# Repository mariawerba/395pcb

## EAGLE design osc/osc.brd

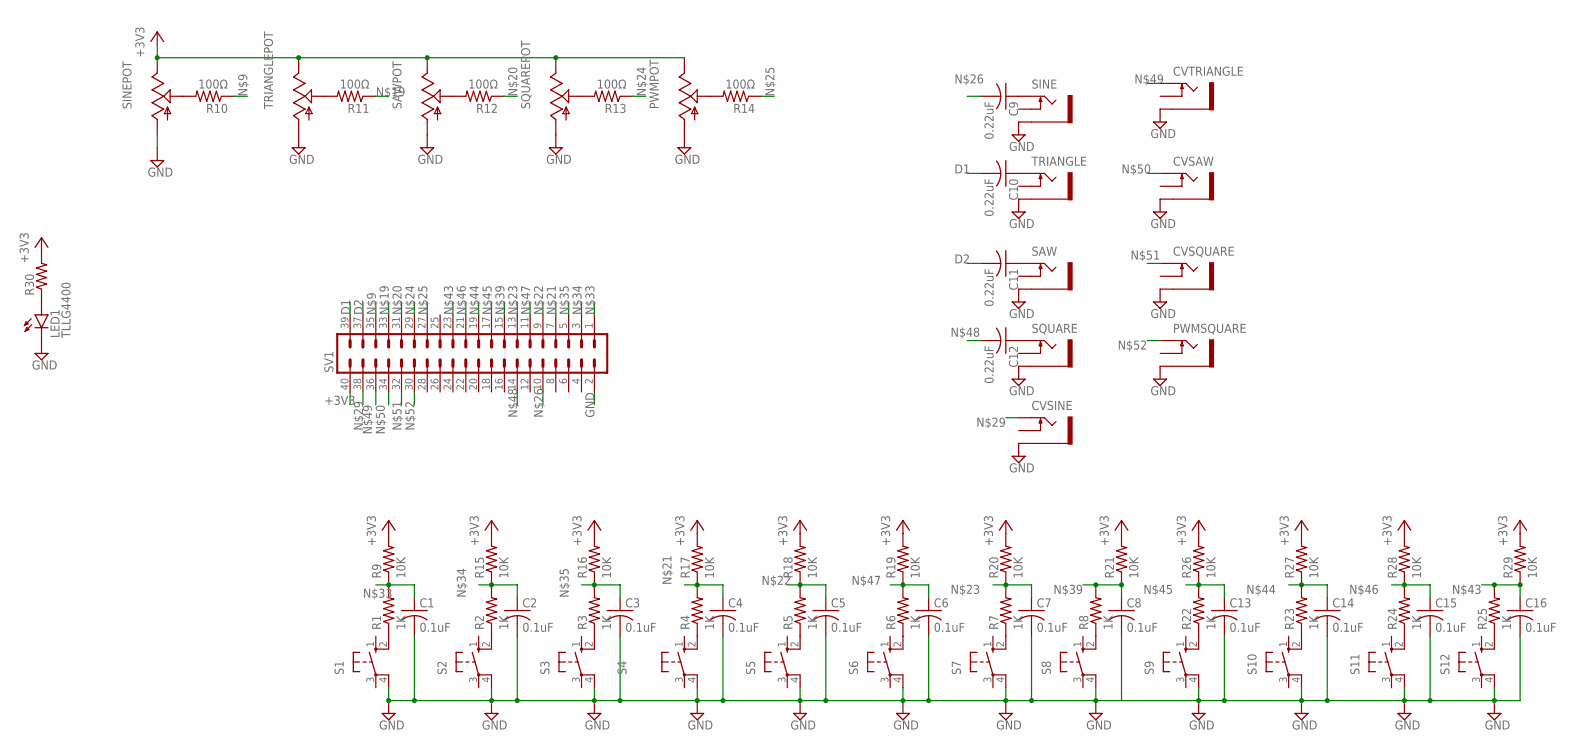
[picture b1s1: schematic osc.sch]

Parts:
C1, C2, C3, C4, C5, C6, C7, C8, C13, C14, C15, C16: 0.1uF; C025-024X044
C9, C10, C11, C12: 0.22uF; C025-024X044
CVSAW: THONKICONNNEW; WQP-PJ301M-12_JACK
CVSINE: THONKICONNNEW; WQP-PJ301M-12_JACK
CVSQUARE: THONKICONNNEW; WQP-PJ301M-12_JACK
CVTRIANGLE: THONKICONNNEW; WQP-PJ301M-12_JACK
LED1: TLLG4400; LED3MM
PWMPOT: 9MM_SNAP-IN_POT_; 9MM_SNAP-IN_POT
PWMSQUARE: THONKICONNNEW; WQP-PJ301M-12_JACK
R1, R2, R3, R4, R5, R6, R7, R8, R22, R23, R24, R25: 1K; 0207/10
R9, R15, R16, R17, R18, R19, R20, R21, R26, R27, R28, R29: 10K; 0207/10
R10, R11, R12, R13, R14: 100Ω; 0207/10
R30: R-US_0207/10; 0207/10
S1, S2, S3, S4, S5, S6, S7, S8, S9, S10, S11, S12: 10-XX; B3F-10XX
SAW: THONKICONNNEW; WQP-PJ301M-12_JACK
SAWPOT: 9MM_SNAP-IN_POT_; 9MM_SNAP-IN_POT
SINE: THONKICONNNEW; WQP-PJ301M-12_JACK
SINEPOT: 9MM_SNAP-IN_POT_; 9MM_SNAP-IN_POT
SQUARE: THONKICONNNEW; WQP-PJ301M-12_JACK
SQUAREPOT: 9MM_SNAP-IN_POT_; 9MM_SNAP-IN_POT
SV1: MA20-2
TRIANGLE: THONKICONNNEW; WQP-PJ301M-12_JACK
TRIANGLEPOT: 9MM_SNAP-IN_POT_; 9MM_SNAP-IN_POT

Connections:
+3V3: PWMPOT.3 (E), R9.2, R15.2, R16.2, R17.2, R18.2, R19.2, R20.2, R21.2, R26.2, R27.2, R28.2, R29.2, R30.2, SAWPOT.3 (E), SINEPOT.3 (E), SQUAREPOT.3 (E), SV1.40, TRIANGLEPOT.3 (E)
D1: C10.2, SV1.39
D2: C11.2, SV1.37
GND: C1.2, C2.2, C3.2, C4.2, C5.2, C6.2, C7.2, C8.2, C13.2, C14.2, C15.2, C16.2, CVSAW.P$3_SLEEVE (SLEEVE), CVSINE.P$3_SLEEVE (SLEEVE), CVSQUARE.P$3_SLEEVE (SLEEVE), CVTRIANGLE.P$3_SLEEVE (SLEEVE), LED1.K (C), PWMPOT.1 (A), PWMSQUARE.P$3_SLEEVE (SLEEVE), S1.4 (P1), S2.4 (P1), S3.4 (P1), S4.4 (P1), S5.4 (P1), S6.4 (P1), S7.4 (P1), S8.4 (P1), S9.4 (P1), S10.4 (P1), S11.4 (P1), S12.4 (P1), SAW.P$3_SLEEVE (SLEEVE), SAWPOT.1 (A), SINE.P$3_SLEEVE (SLEEVE), SINEPOT.1 (A), SQUARE.P$3_SLEEVE (SLEEVE), SQUAREPOT.1 (A), SV1.2, TRIANGLE.P$3_SLEEVE (SLEEVE), TRIANGLEPOT.1 (A)
unnamed: R1.1, S1.2 (S1)
unnamed: R2.1, S2.2 (S1)
unnamed: R3.1, S3.2 (S1)
unnamed: R4.1, S4.2 (S1)
unnamed: R6.1, S6.2 (S1)
unnamed: R7.1, S7.2 (S1)
unnamed: R8.1, S8.2 (S1)
unnamed: R5.1, S5.2 (S1)
unnamed: R10.1, SV1.35
unnamed: C9.1, SINE.P$1_TIP (TIP)
unnamed: C10.1, TRIANGLE.P$1_TIP (TIP)
unnamed: C11.1, SAW.P$1_TIP (TIP)
unnamed: C12.1, SQUARE.P$1_TIP (TIP)
unnamed: R10.2, SINEPOT.2 (S)
unnamed: R11.2, TRIANGLEPOT.2 (S)
unnamed: R12.2, SAWPOT.2 (S)
unnamed: R13.2, SQUAREPOT.2 (S)
unnamed: PWMPOT.2 (S), R14.2
unnamed: R11.1, SV1.33
unnamed: R12.1, SV1.31
unnamed: C4.1, R4.2, R17.1, SV1.7
unnamed: C5.1, R5.2, R18.1, SV1.9
unnamed: C7.1, R7.2, R20.1, SV1.13
unnamed: R13.1, SV1.29
unnamed: R14.1, SV1.27
unnamed: C9.2, SV1.10
unnamed: LED1.A, R30.1
unnamed: CVSINE.P$1_TIP (TIP), SV1.38
unnamed: C1.1, R1.2, R9.1, SV1.1
unnamed: C2.1, R2.2, R15.1, SV1.3
unnamed: C3.1, R3.2, R16.1, SV1.5
unnamed: R23.1, S10.2 (S1)
unnamed: C8.1, R8.2, R21.1, SV1.15
unnamed: R24.1, S11.2 (S1)
unnamed: R25.1, S12.2 (S1)
unnamed: R22.1, S9.2 (S1)
unnamed: C16.1, R25.2, R29.1, SV1.23
unnamed: C14.1, R23.2, R27.1, SV1.19
unnamed: C13.1, R22.2, R26.1, SV1.17
unnamed: C15.1, R24.2, R28.1, SV1.21
unnamed: C6.1, R6.2, R19.1, SV1.11
unnamed: C12.2, SV1.14
unnamed: CVTRIANGLE.P$1_TIP (TIP), SV1.36
unnamed: CVSAW.P$1_TIP (TIP), SV1.34
unnamed: CVSQUARE.P$1_TIP (TIP), SV1.32
unnamed: PWMSQUARE.P$1_TIP (TIP), SV1.30

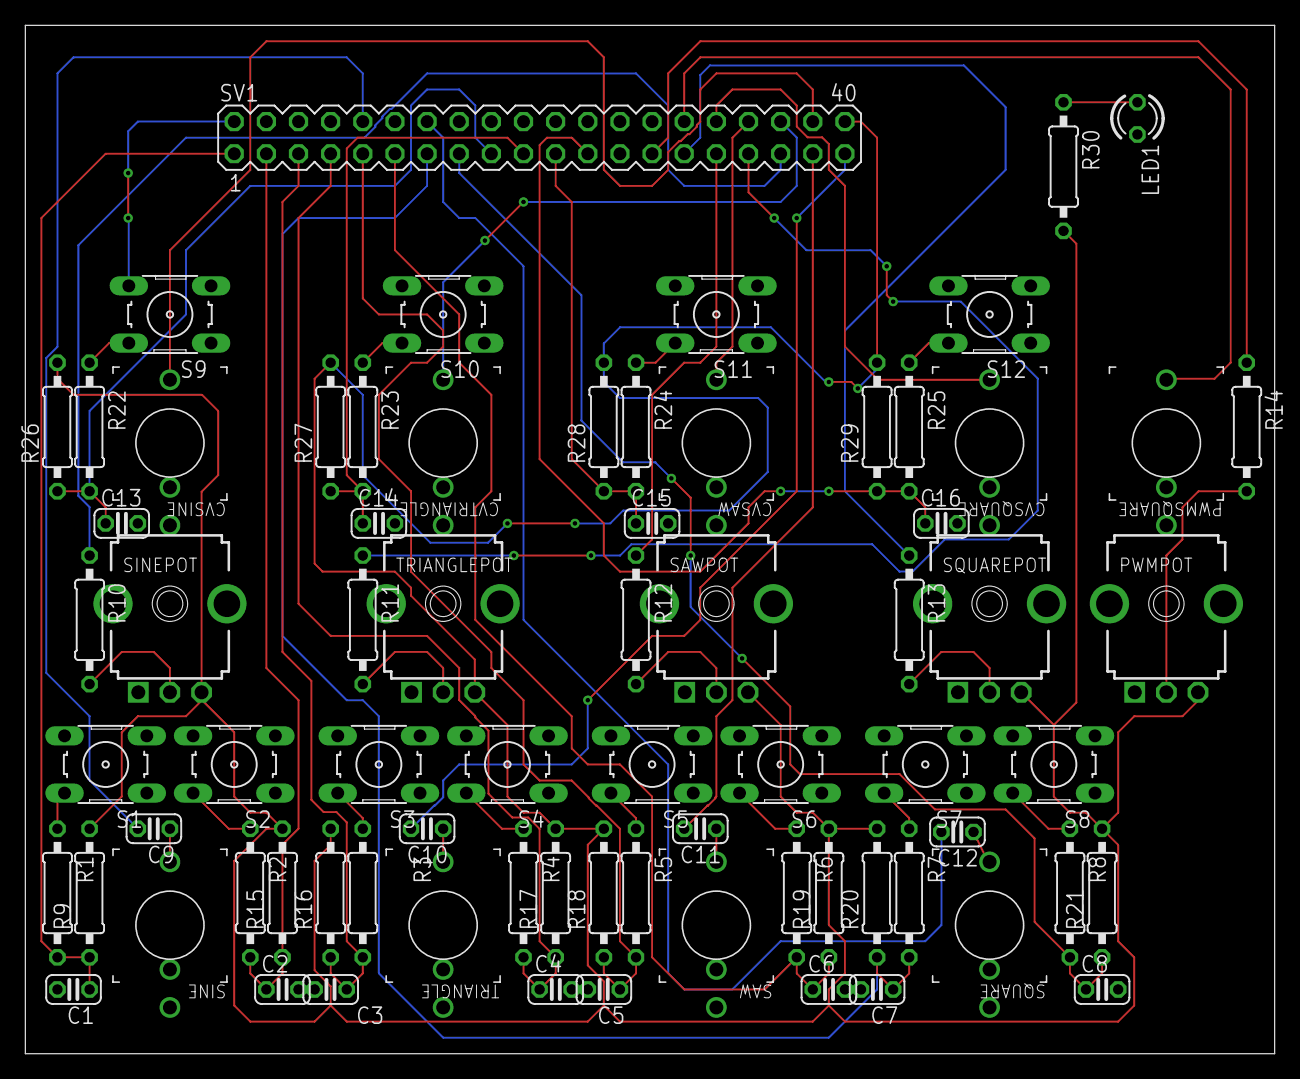
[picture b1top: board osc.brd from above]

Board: 2 copper layers, 98.7 x 81.3 mm, 74 parts (0 on the bottom side), 50 nets.

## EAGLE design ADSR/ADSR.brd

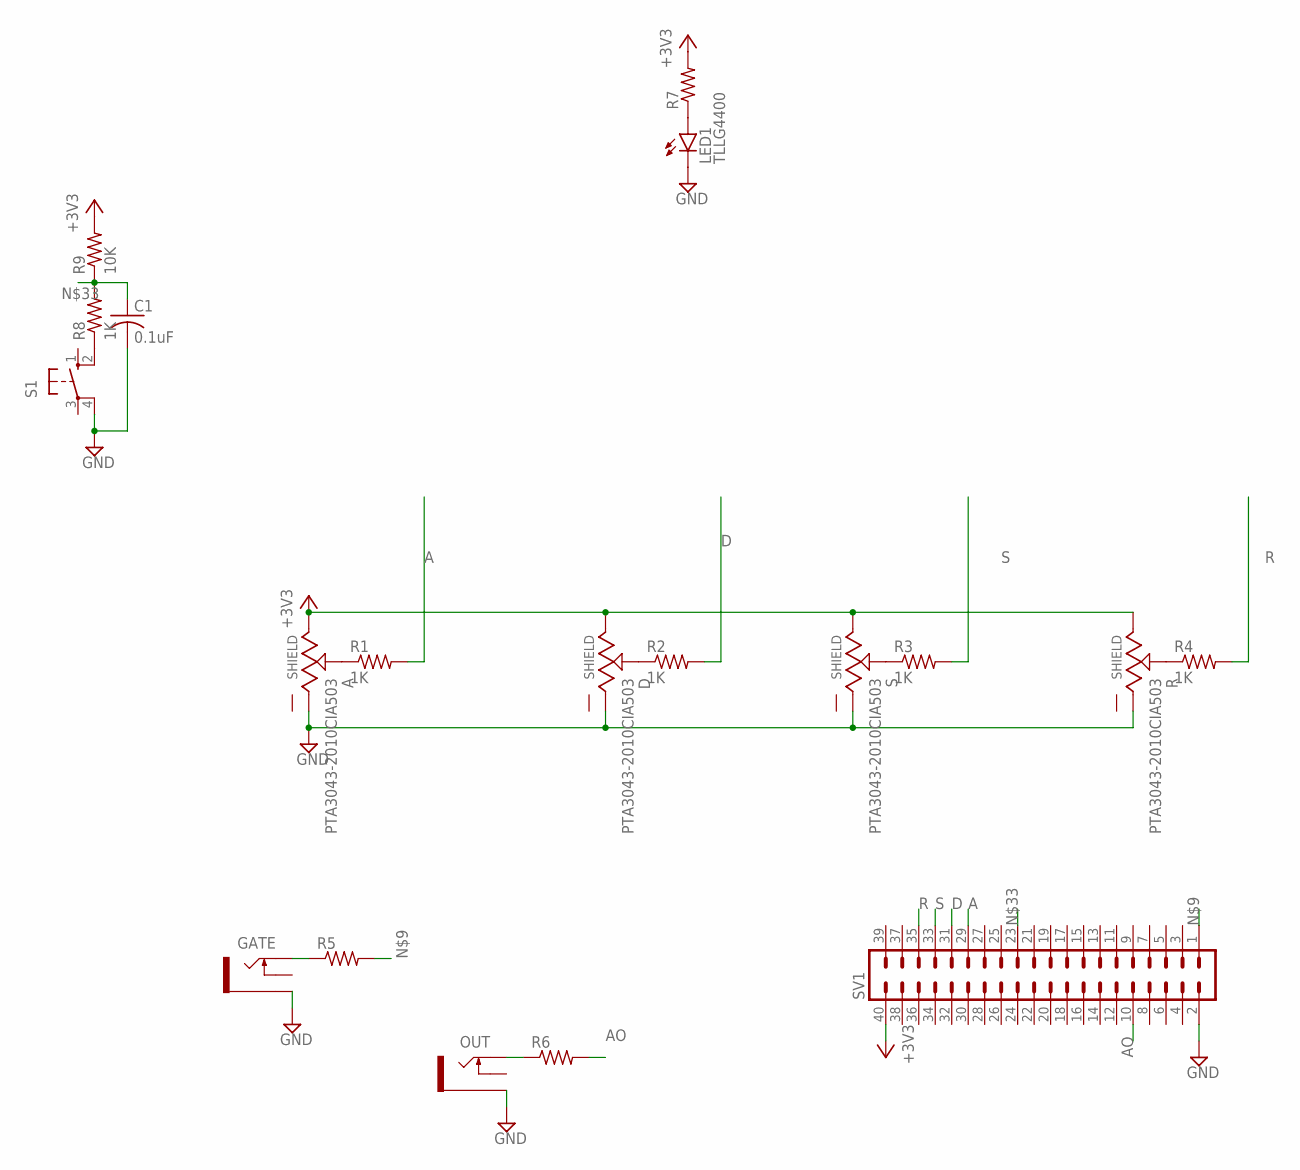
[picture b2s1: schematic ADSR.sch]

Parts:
A: PTA3043-2010CIA503; TRIM_PTA3043-2010CIA503
C1: 0.1uF; C025-024X044
D: PTA3043-2010CIA503; TRIM_PTA3043-2010CIA503
GATE: THONKICONNNEW; WQP-PJ301M-12_JACK
LED1: TLLG4400; LED3MM
OUT: THONKICONNNEW; WQP-PJ301M-12_JACK
R: PTA3043-2010CIA503; TRIM_PTA3043-2010CIA503
R1, R2, R3, R4, R8: 1K; 0207/10
R5, R6, R7: R-US_0207/10; 0207/10
R9: 10K; 0207/10
S: PTA3043-2010CIA503; TRIM_PTA3043-2010CIA503
S1: 10-XX; B3F-10XX
SV1: MA20-2

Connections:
+3V3: A.1, D.1, R.1, R7.2, R9.2, S.1, SV1.40
A: R1.2, SV1.29
AO: R6.2, SV1.10
D: R2.2, SV1.31
GND: A.3, C1.2, D.3, GATE.P$3_SLEEVE (SLEEVE), LED1.K (C), OUT.P$3_SLEEVE (SLEEVE), R.3, S.3, S1.4 (P1), SV1.2
unnamed: A.2, R1.1
unnamed: D.2, R2.1
unnamed: R3.1, S.2
unnamed: R.2, R4.1
unnamed: OUT.P$1_TIP (TIP), R6.1
unnamed: LED1.A, R7.1
unnamed: R8.1, S1.2 (S1)
unnamed: R5.2, SV1.1
unnamed: GATE.P$1_TIP (TIP), R5.1
unnamed: C1.1, R8.2, R9.1, SV1.23
R: R4.2, SV1.35
S: R3.2, SV1.33

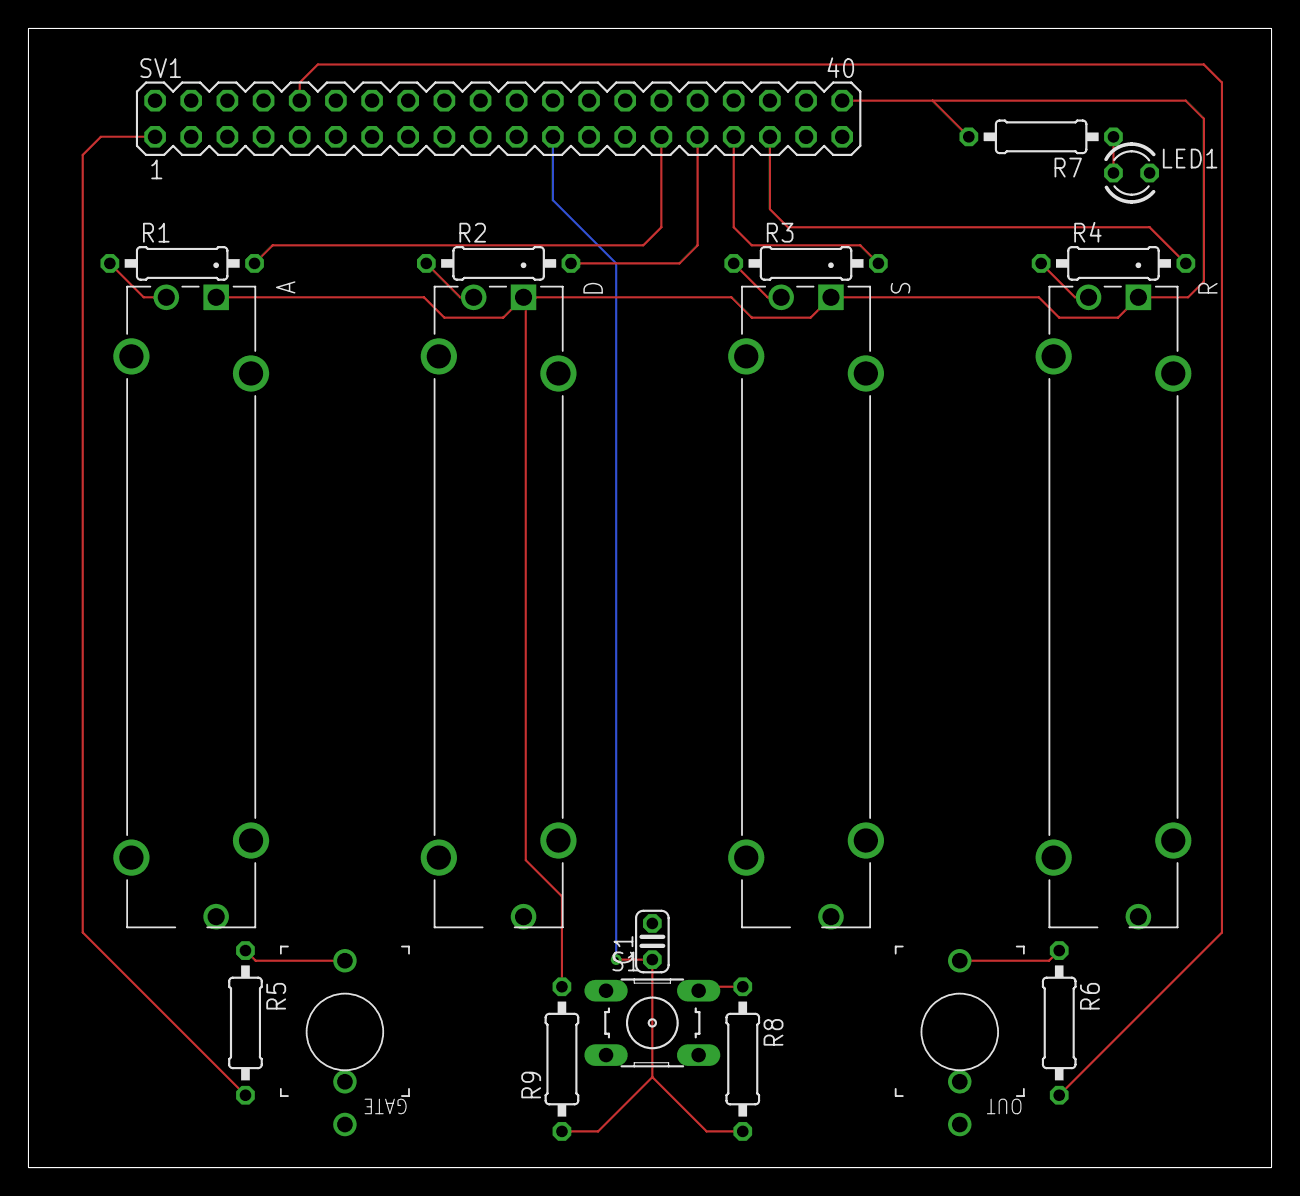
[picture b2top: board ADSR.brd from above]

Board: 2 copper layers, 87.3 x 80.0 mm, 19 parts (0 on the bottom side), 17 nets.

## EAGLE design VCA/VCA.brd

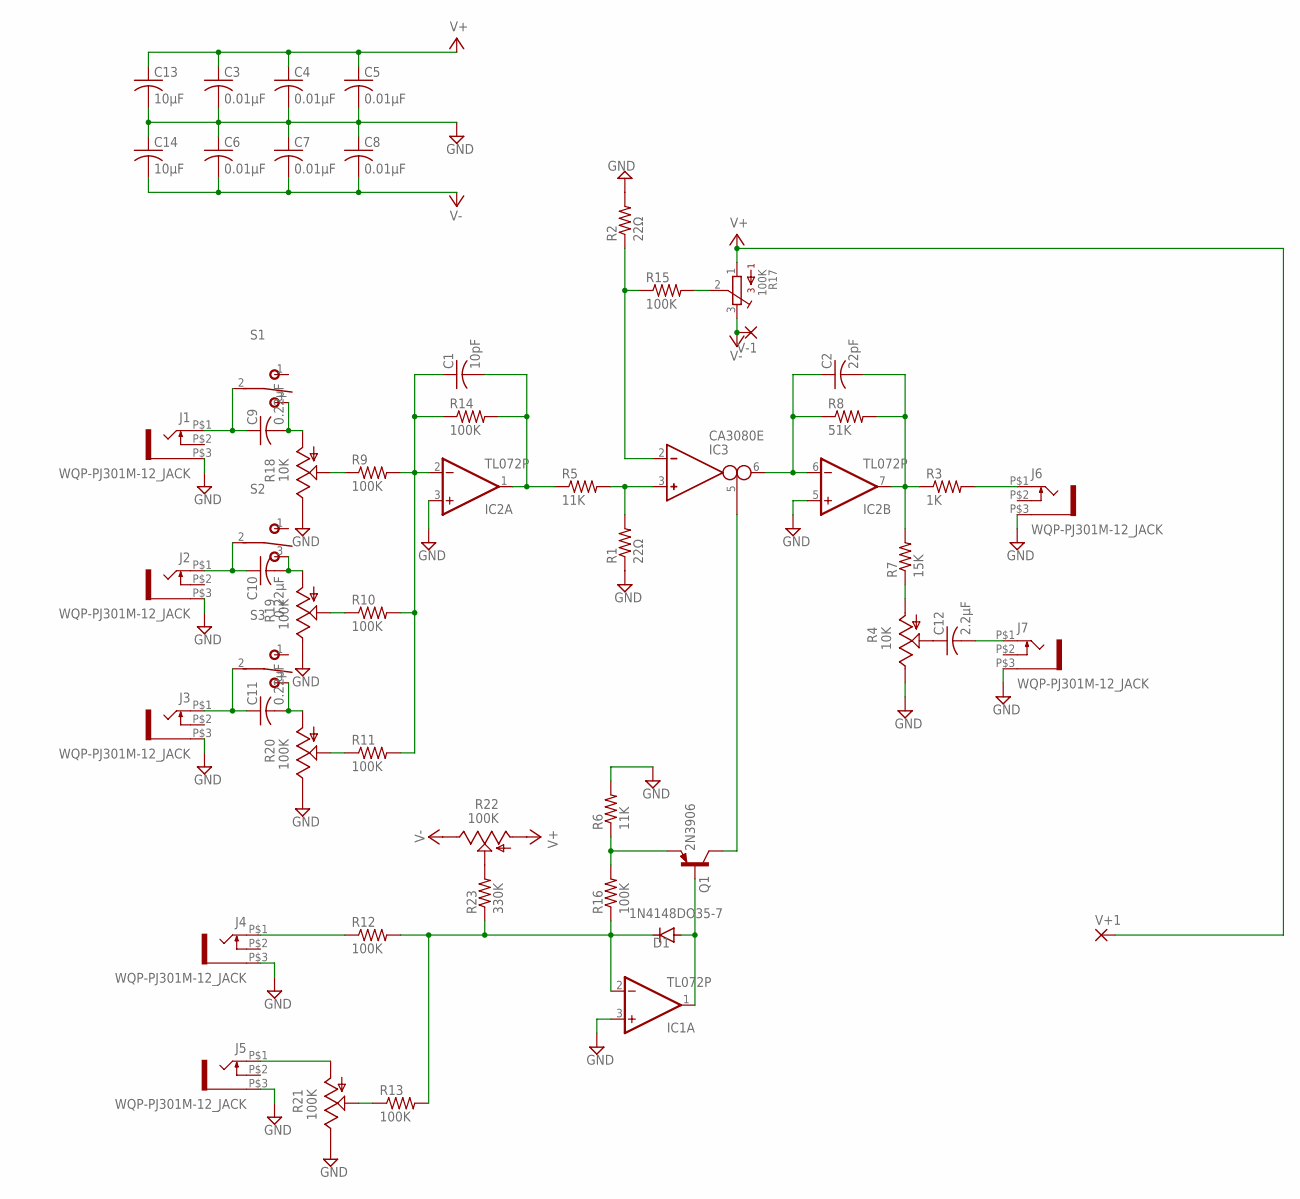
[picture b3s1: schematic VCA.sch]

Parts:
C1: 10pF; C025-024X044
C2: 22pF; C025-024X044
C3, C4, C5, C6, C7, C8: 0.01μF; C025-024X044
C9, C10, C11: 0.22μF; C025-024X044
C12: 2.2μF; C025-024X044
C13, C14: 10μF; C025-024X044
D1: 1N4148DO35-7; DO35-7
IC1, IC2: TL072P; DIL08
IC3: CA3080E; DIL08
J1, J2, J3, J4, J5, J6, J7: WQP-PJ301M-12_JACK
Q1: 2N3906; TO92
R1, R2: 22Ω; 0411/15
R3: 1K; 0411/15
R4, R18: 10K; 9MM_SNAP-IN_POT
R5, R6: 11K; 0411/15
R7: 15K; 0411/15
R8: 51K; 0411/15
R9, R10, R11, R12, R13, R14, R15, R16: 100K; 0411/15
R17: 100K; 3386C
R19, R20, R21, R22: 100K; 9MM_SNAP-IN_POT
R23: 330K; 0411/15
S1, S2, S3: T-80-T-SPDT-ON-OFF-ON; M9040P
V+1: 1,6/0,8
V-1: 1,6/0,8

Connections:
GND: C3.2, C4.2, C5.2, C6.1, C7.1, C8.1, C13.2, C14.1, IC1.3 (+IN), IC2.3 (+IN), IC2.5 (+IN), J1.P$3 (1), J2.P$3 (1), J3.P$3 (1), J4.P$3 (1), J5.P$3 (1), J6.P$3 (1), J7.P$3 (1), R1.1, R2.2, R4.3 (E), R6.2, R18.3 (E), R19.3 (E), R20.3 (E), R21.3 (E)
unnamed: C2.1, IC2.6 (-IN), IC3.6 (OUT), R8.1
unnamed: IC3.3 (IN_P), R1.2, R5.2
unnamed: C1.2, IC2.1 (OUT), R5.1, R14.2
unnamed: C2.2, IC2.7 (OUT), R3.1, R7.2, R8.2
unnamed: Q1.3 (E), R6.1, R16.2
unnamed: IC3.2 (IN_N), R2.1, R15.1
unnamed: C1.1, IC2.2 (-IN), R9.2, R10.2, R11.2, R14.1
unnamed: D1.A, IC1.1 (OUT), Q1.2 (B)
unnamed: IC3.5 (I_BIAS), Q1.1 (C)
unnamed: D1.C, IC1.2 (-IN), R12.2, R13.2, R16.1, R23.1
unnamed: C9.1, J1.P$1 (2), S1.2
unnamed: C10.1, J2.P$1 (2), S2.2
unnamed: C11.1, J3.P$1 (2), S3.2
unnamed: J4.P$1 (2), R12.1
unnamed: C12.2, J7.P$1 (2)
unnamed: J6.P$1 (2), R3.2
unnamed: R4.1 (A), R7.1
unnamed: C12.1, R4.2 (S)
unnamed: R15.2, R17.2
unnamed: R9.1, R18.2 (S)
unnamed: C9.2, R18.1 (A), S1.3 (S)
unnamed: C10.2, R19.1 (A), S2.3 (S)
unnamed: C11.2, R20.1 (A), S3.3 (S)
unnamed: R11.1, R20.2 (S)
unnamed: J5.P$1 (2), R21.1 (A)
unnamed: R10.1, R19.2 (S)
unnamed: R13.1, R21.2 (S)
unnamed: R22.2 (S), R23.2
V+: C3.1, C4.1, C5.1, C13.1, IC1.8 (V+), IC2.8 (V+), R17.1, R22.1 (A), V+1.1
V-: C6.2, C7.2, C8.2, C14.2, IC1.4 (V-), IC2.4 (V-), R17.3, R22.3 (E), V-1.1

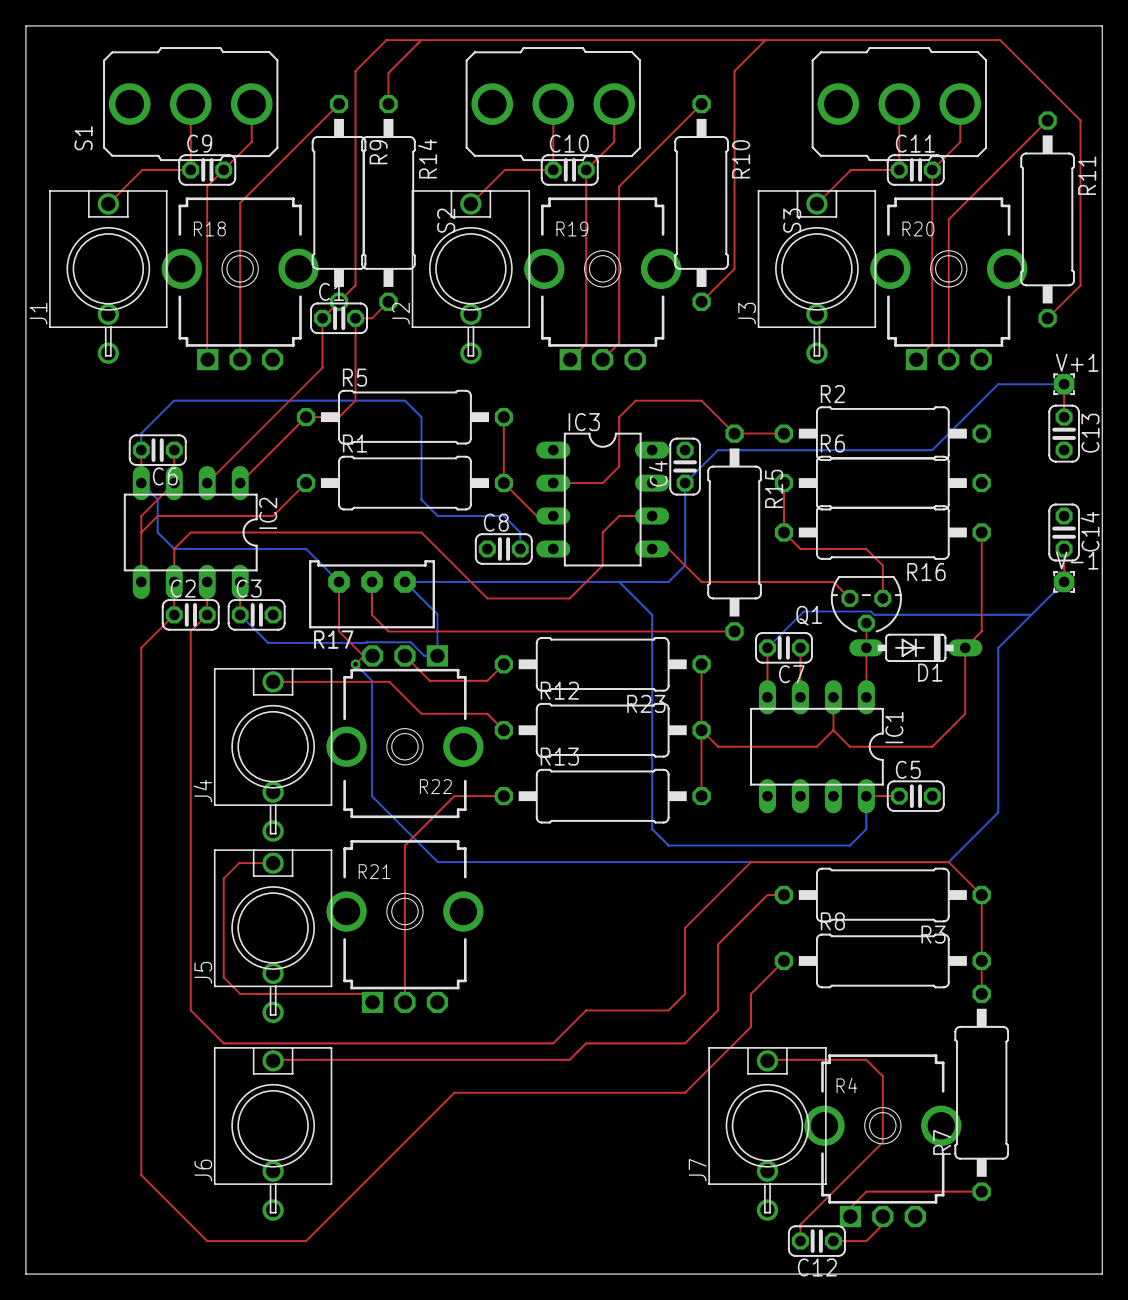
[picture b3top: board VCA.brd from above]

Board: 2 copper layers, 83.0 x 96.2 mm, 54 parts (0 on the bottom side), 31 nets.

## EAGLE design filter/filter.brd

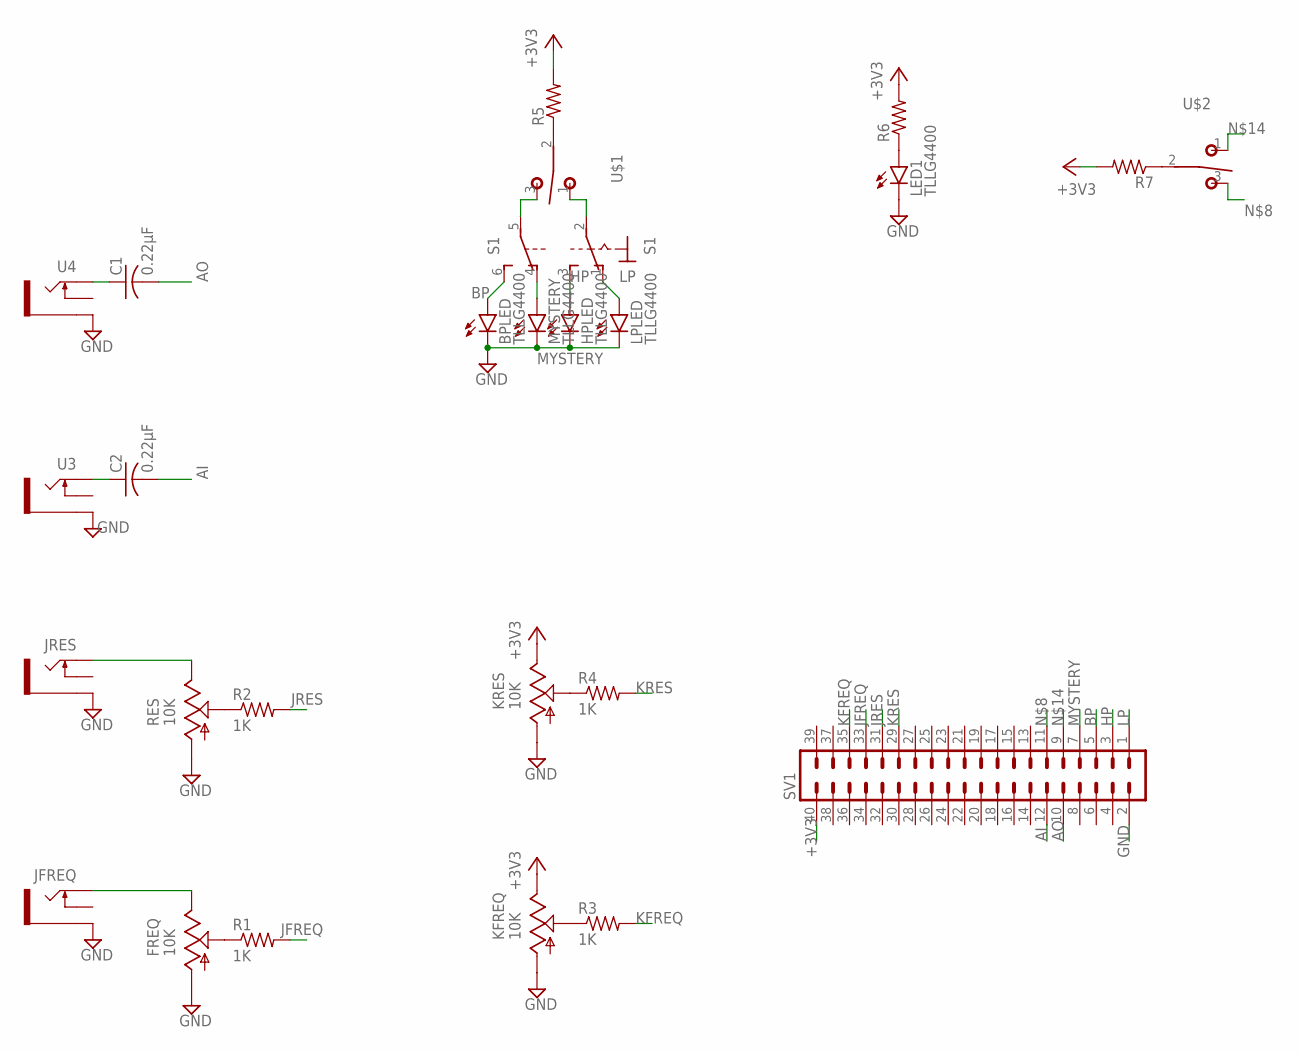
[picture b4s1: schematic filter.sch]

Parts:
BPLED: TLLG4400; LED3MM
C1, C2: 0.22μF; C025-024X044
FREQ: 10K; 9MM_SNAP-IN_POT
HPLED: TLLG4400; LED3MM
JFREQ: THONKICONNNEW; WQP-PJ301M-12_JACK
JRES: THONKICONNNEW; WQP-PJ301M-12_JACK
KFREQ: 10K; 9MM_SNAP-IN_POT
KRES: 10K; 9MM_SNAP-IN_POT
LED1: TLLG4400; LED3MM
LPLED: TLLG4400; LED3MM
MYSTERY: TLLG4400; LED3MM
R1, R2, R3, R4: 1K; 0207/10
R5, R6, R7: R-US_0207/10; 0207/10
RES: 10K; 9MM_SNAP-IN_POT
S1: 320-938
SV1: MA20-2
U3, U4: THONKICONNNEW; WQP-PJ301M-12_JACK
U$1, U$2: T-80-T-SPDT-ON-OFF-ON; M9040P

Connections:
+3V3: KFREQ.3 (E), KRES.3 (E), R5.2, R6.2, R7.2, SV1.40
AI: C2.2, SV1.12
AO: C1.2, SV1.10
BP: BPLED.A, S1.6 (S), SV1.5
GND: BPLED.K (C), FREQ.1 (A), HPLED.K (C), JFREQ.P$3_SLEEVE (SLEEVE), JRES.P$3_SLEEVE (SLEEVE), KFREQ.1 (A), KRES.1 (A), LED1.K (C), LPLED.K (C), MYSTERY.K (C), RES.1 (A), SV1.2, U3.P$3_SLEEVE (SLEEVE), U4.P$3_SLEEVE (SLEEVE)
HP: HPLED.A, S1.3 (S), SV1.3
JFREQ: R1.2, SV1.33
JRES: R2.2, SV1.31
KFREQ: R3.2, SV1.35
KRES: R4.2, SV1.29
LP: LPLED.A, S1.1 (O), SV1.1
MYSTERY: MYSTERY.A, S1.4 (O), SV1.7
unnamed: FREQ.2 (S), R1.1
unnamed: R2.1, RES.2 (S)
unnamed: KFREQ.2 (S), R3.1
unnamed: KRES.2 (S), R4.1
unnamed: C1.1, U4.P$1_TIP (TIP)
unnamed: LED1.A, R6.1
unnamed: C2.1, U3.P$1_TIP (TIP)
unnamed: SV1.11, U$2.3 (S)
unnamed: JRES.P$1_TIP (TIP), RES.3 (E)
unnamed: FREQ.3 (E), JFREQ.P$1_TIP (TIP)
unnamed: S1.5, U$1.3 (S)
unnamed: S1.2, U$1.1 (O)
unnamed: R5.1, U$1.2
unnamed: SV1.9, U$2.1 (O)
unnamed: R7.1, U$2.2

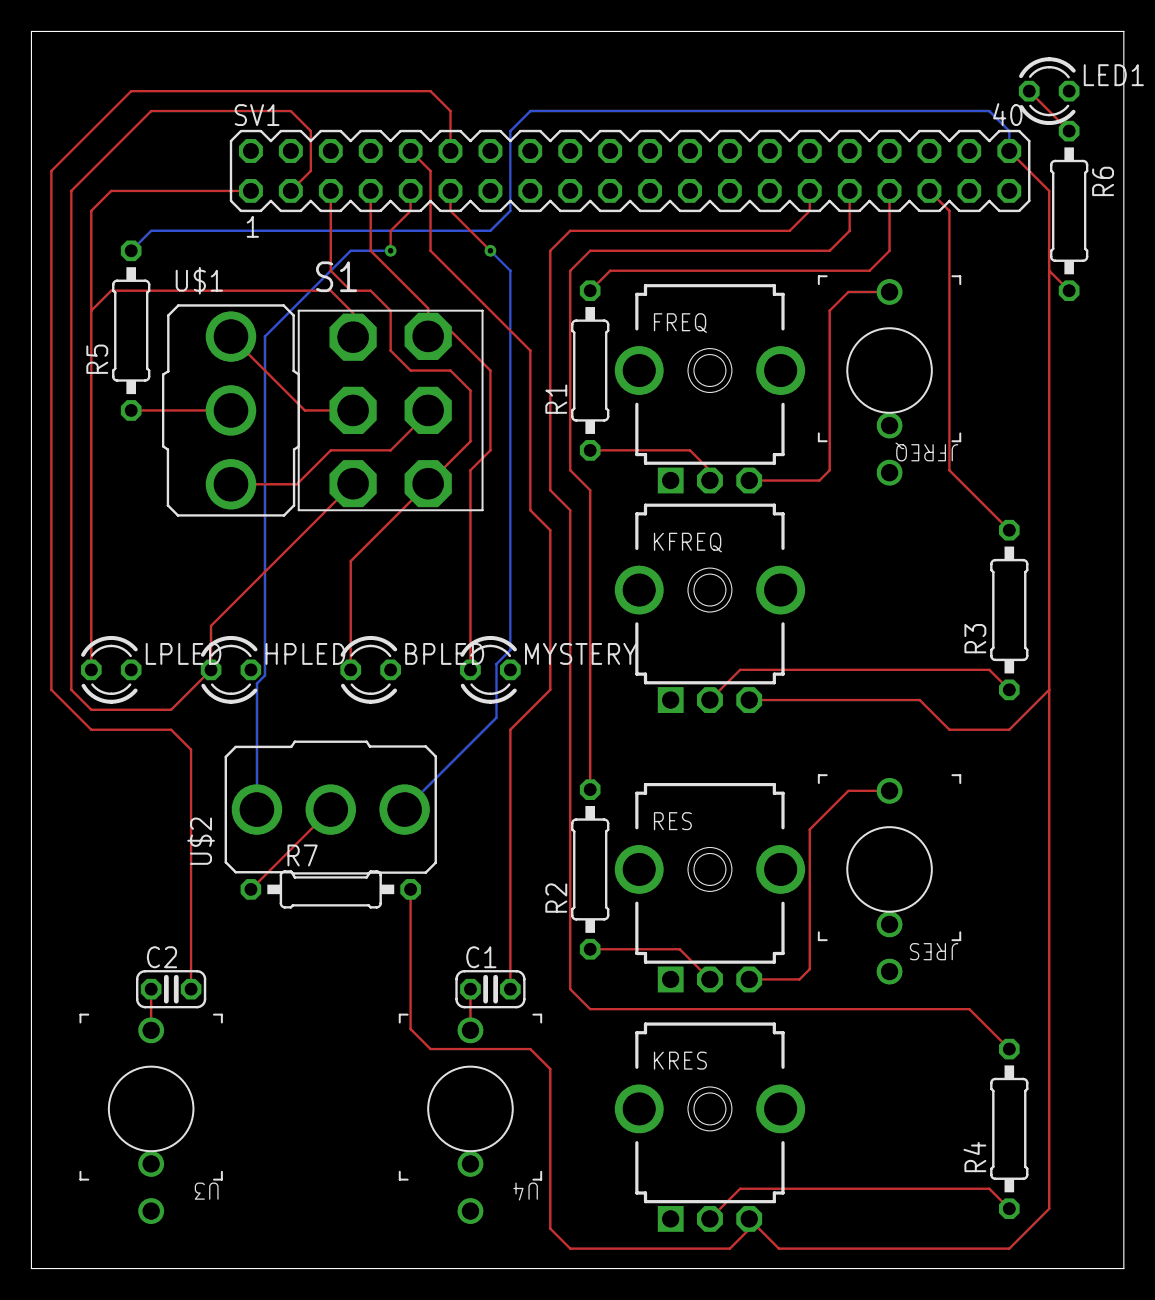
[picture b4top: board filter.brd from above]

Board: 2 copper layers, 69.5 x 78.7 mm, 26 parts (0 on the bottom side), 27 nets.

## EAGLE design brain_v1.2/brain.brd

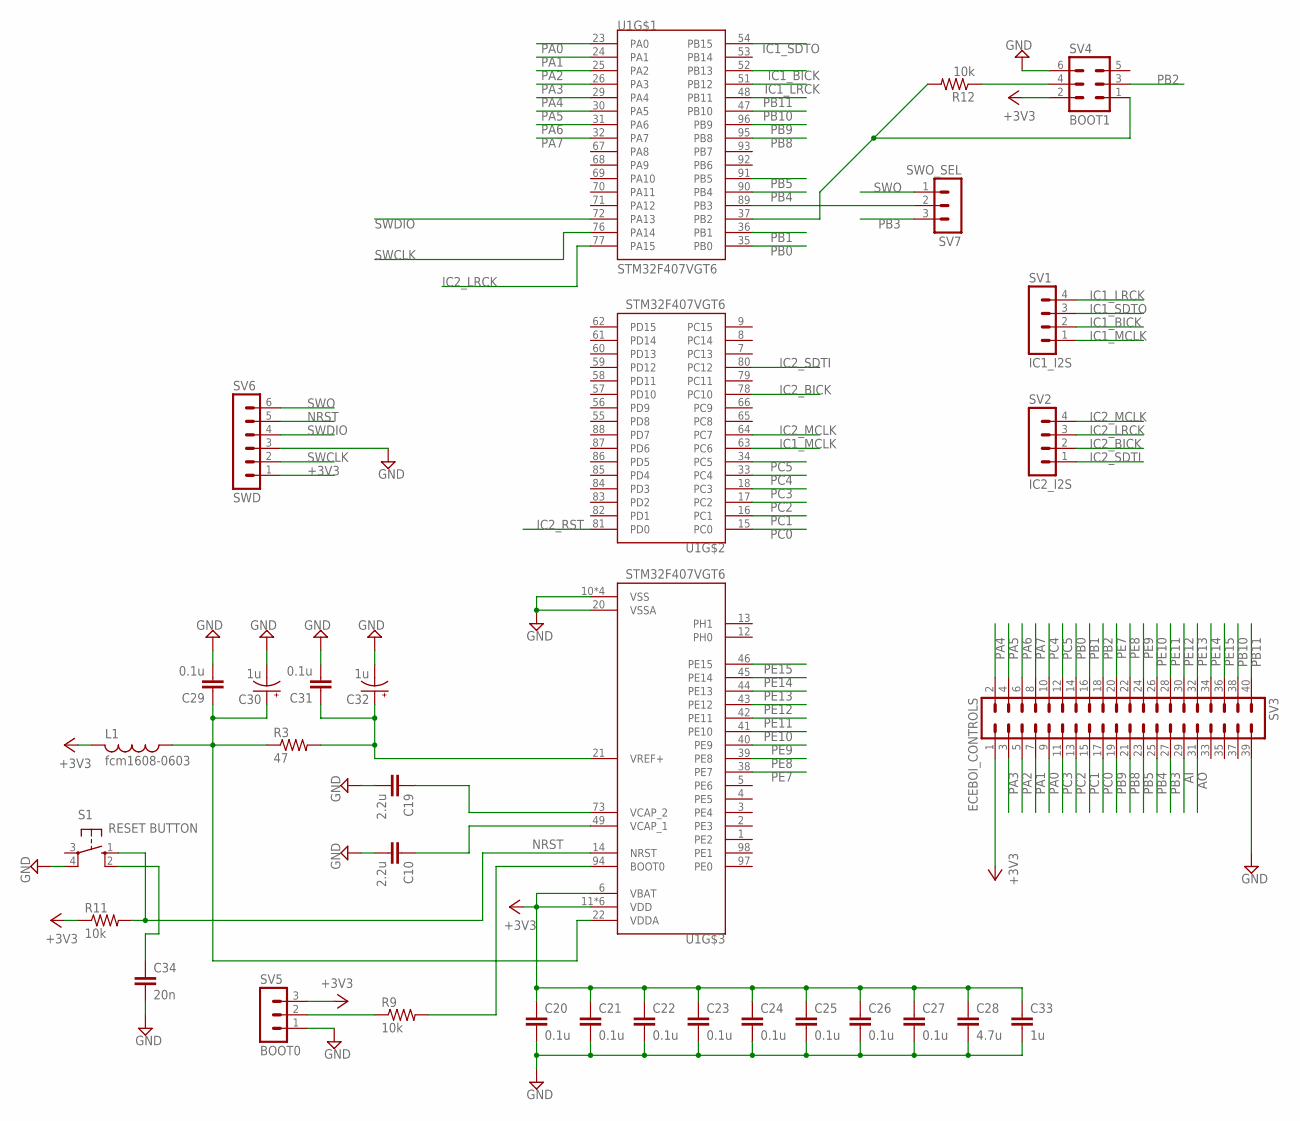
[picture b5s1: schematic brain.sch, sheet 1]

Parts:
C10, C19: 2.2u; C025-024X044
C20, C21, C22, C23, C24, C25, C26, C27, C29, C31: 0.1u; C025-024X044
C28: 4.7u; C025-024X044
C30, C32: 1u; E2-5
C33: 1u; C025-024X044
C34: 20n; C025-024X044
L1: fcm1608-0603; 0207/10
R3: 47; 0207/10
R9, R11, R12: 10k; 0207/10
S1: RESET BUTTON; B3F-10XX
SV1: IC1_I2S; MA04-1
SV2: IC2_I2S; MA04-1
SV3: ECEBOI_CONTROLS; MA20-2
SV4: BOOT1; MA03-2
SV5: BOOT0; MA03-1
SV6: SWD; MA06-1
SV7: SWO_SEL; MA03-1
U1: STM32F407VGT6; QFP50P1600X1600X160-100N

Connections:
+3V3: C20.1, C21.1, C22.1, C23.1, C24.1, C25.1, C26.1, C27.1, C28.1, C33.1, L1.2, R11.1, SV3.1, SV4.2, SV5.3, SV6.1, U1.6 (VBAT), U1.11 (VDD), U1.19 (VDD), U1.28 (VDD), U1.50 (VDD), U1.75 (VDD), U1.100 (VDD); also elsewhere on the board
AI: SV3.29; also elsewhere on the board
AO: SV3.31; also elsewhere on the board
GND: C10.2, C19.2, C20.2, C21.2, C22.2, C23.2, C24.2, C25.2, C26.2, C27.2, C28.2, C29.2, C30.-, C31.2, C32.-, C33.2, C34.2, S1.4 (P1), SV3.39, SV4.6, SV5.1, SV6.3, U1.10 (VSS), U1.20 (VSSA), U1.27 (VSS), U1.74 (VSS), U1.99 (VSS); also elsewhere on the board
IC1_BICK: SV1.2, U1.52 (PB13); also elsewhere on the board
IC1_LRCK: SV1.4, U1.51 (PB12); also elsewhere on the board
IC1_MCLK: SV1.1, U1.63 (PC6); also elsewhere on the board
IC1_SDTO: SV1.3, U1.54 (PB15); also elsewhere on the board
IC2_BICK: SV2.2, U1.78 (PC10); also elsewhere on the board
IC2_LRCK: SV2.3, U1.77 (PA15); also elsewhere on the board
IC2_MCLK: SV2.4, U1.64 (PC7); also elsewhere on the board
IC2_RST: U1.81 (PD0); also elsewhere on the board
IC2_SDTI: SV2.1, U1.80 (PC12); also elsewhere on the board
unnamed: R12.1, SV4.4
unnamed: C10.1, U1.49 (VCAP_1)
unnamed: C19.1, U1.73 (VCAP_2)
unnamed: C29.1, C30.+, L1.1, R3.1, U1.22 (VDDA)
unnamed: C31.1, C32.+, R3.2, U1.21 (VREF+)
unnamed: R12.2, SV4.1, U1.37 (PB2)
unnamed: R9.1, SV5.2
unnamed: R9.2, U1.94 (BOOT0)
unnamed: C34.1, S1.2 (S1)
unnamed: SV7.2, U1.89 (PB3)
NRST: R11.2, S1.1 (S), SV6.5, U1.14 (NRST)
PA0: SV3.9, U1.23 (PA0)
PA1: SV3.7, U1.24 (PA1)
PA2: SV3.5, U1.25 (PA2)
PA3: SV3.3, U1.26 (PA3)
PA4: SV3.2, U1.29 (PA4)
PA5: SV3.4, U1.30 (PA5)
PA6: SV3.6, U1.31 (PA6)
PA7: SV3.8, U1.32 (PA7)
PB0: SV3.14, U1.35 (PB0)
PB1: SV3.16, U1.36 (PB1)
PB2: SV3.18, SV4.3
PB3: SV3.27, SV7.3
PB4: SV3.25, U1.90 (PB4)
PB5: SV3.23, U1.91 (PB5)
PB8: SV3.21, U1.95 (PB8)
PB9: SV3.19, U1.96 (PB9)
PB10: SV3.38, U1.47 (PB10)
PB11: SV3.40, U1.48 (PB11)
PC0: SV3.17, U1.15 (PC0)
PC1: SV3.15, U1.16 (PC1)
PC2: SV3.13, U1.17 (PC2)
PC3: SV3.11, U1.18 (PC3)
PC4: SV3.10, U1.33 (PC4)
PC5: SV3.12, U1.34 (PC5)
PE7: SV3.20, U1.38 (PE7)
PE8: SV3.22, U1.39 (PE8)
PE9: SV3.24, U1.40 (PE9)
PE10: SV3.26, U1.41 (PE10)
PE11: SV3.28, U1.42 (PE11)
PE12: SV3.30, U1.43 (PE12)
PE13: SV3.32, U1.44 (PE13)
PE14: SV3.34, U1.45 (PE14)
PE15: SV3.36, U1.46 (PE15)
SWCLK: SV6.2, U1.76 (PA14)
SWDIO: SV6.4, U1.72 (PA13)
SWO: SV6.6, SV7.1

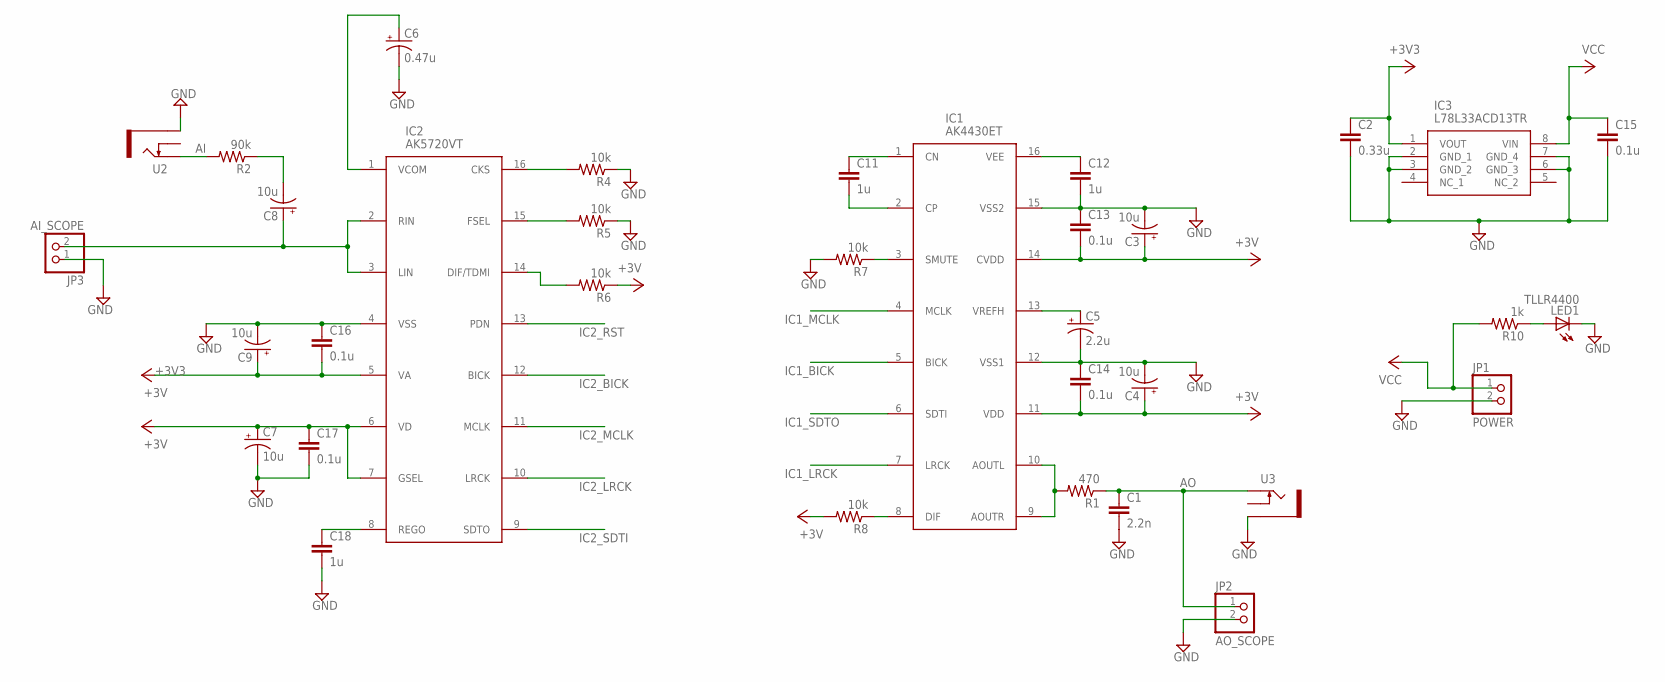
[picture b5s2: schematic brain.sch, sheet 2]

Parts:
C1: 2.2n; C025-024X044
C2: 0.33u; C025-024X044
C3, C4, C7, C8, C9: 10u; E2-5
C5: 2.2u; E2-5
C6: 0.47u; E2-5
C11, C12, C18: 1u; C025-024X044
C13, C14, C15, C16, C17: 0.1u; C025-024X044
IC1: AK4430ET; SOP65P640X110-16N
IC2: AK5720VT; SOP65P640X110-16N
IC3: L78L33ACD13TR; SOIC127P600X175-8N
JP1: POWER; 1X02
JP2: AO_SCOPE; 1X02
JP3: AI_SCOPE; 1X02
LED1: TLLR4400; LED3MM
R1: 470; 0207/10
R2: 90k; 0207/10
R4, R5, R6, R7, R8: 10k; 0207/10
R10: 1k; 0207/10
U2, U3: THONKICONNNEW; WQP-PJ301M-12_JACK

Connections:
+3V3: C2.1, C3.+, C4.+, C7.+, C9.+, C13.2, C14.2, C16.2, C17.1, IC1.11 (VDD), IC1.14 (CVDD), IC2.5 (VA), IC2.6 (VD), IC2.7 (GSEL), IC3.1 (VOUT), R6.1, R8.2; also elsewhere on the board
AI: R2.2, U2.P$1_TIP (TIP); also elsewhere on the board
AO: C1.1, JP2.1, R1.1, U3.P$1_TIP (TIP); also elsewhere on the board
DIF: IC2.14 (DIF/TDMI), R6.2
GND: C1.2, C2.2, C3.-, C4.-, C5.-, C6.-, C7.-, C9.-, C12.2, C13.1, C14.1, C15.2, C16.1, C17.2, C18.2, IC1.12 (VSS1), IC1.15 (VSS2), IC2.4 (VSS), IC3.2 (GND_1), IC3.3 (GND_2), IC3.6 (GND_3), IC3.7 (GND_4), JP1.2, JP2.2, JP3.1, LED1.K (C), R4.1, R5.1, R7.2, U2.P$3_SLEEVE (SLEEVE), U3.P$3_SLEEVE (SLEEVE); also elsewhere on the board
IC1_BICK: IC1.5 (BICK); also elsewhere on the board
IC1_LRCK: IC1.7 (LRCK); also elsewhere on the board
IC1_MCLK: IC1.4 (MCLK); also elsewhere on the board
IC1_SDTO: IC1.6 (SDTI); also elsewhere on the board
IC2_BICK: IC2.12 (BICK); also elsewhere on the board
IC2_LRCK: IC2.10 (LRCK); also elsewhere on the board
IC2_MCLK: IC2.11 (MCLK); also elsewhere on the board
IC2_RST: IC2.13 (PDN); also elsewhere on the board
IC2_SDTI: IC2.9 (SDTO); also elsewhere on the board
unnamed: C12.1, IC1.16 (VEE)
unnamed: C18.1, IC2.8 (REGO)
unnamed: C11.1, IC1.1 (CN)
unnamed: C11.2, IC1.2 (CP)
unnamed: C8.+, IC2.2 (RIN), IC2.3 (LIN), JP3.2
unnamed: C6.+, IC2.1 (VCOM)
unnamed: IC1.9 (AOUTR), IC1.10 (AOUTL), R1.2
unnamed: C5.+, IC1.13 (VREFH)
unnamed: C8.-, R2.1
unnamed: IC2.16 (CKS), R4.2
unnamed: IC2.15 (FSEL), R5.2
unnamed: IC1.8 (DIF), R8.1
unnamed: IC1.3 (SMUTE), R7.1
unnamed: LED1.A, R10.1
VCC: C15.1, IC3.8 (VIN), JP1.1, R10.2
